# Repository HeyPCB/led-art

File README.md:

# HeyPCB LED Art

Shaped LED boards inspired by films: stars, ghosts, cats, rockets, gears, moons, saucers and shields, each in its own colour. KiCad 10, JLCPCB-ready, CERN-OHL-S-2.0.

<p align="center">                                                 </p>

Every board is its own silhouette and solder-mask colour, with addressable RGB LEDs (XL-2020RGBC-2812B, WS2812B-2020 class) following its outline, a CH32V003 RISC-V controller running at 5 V (so it drives the LEDs directly), a MODE button, a 1-wire SWIO programming header, a 3-pin OUT header that chains the light onto the next board, and USB-C power on a tab at the bottom. 4 layers.

| Board | Idea | Mask | Size | DRC errors / unconnected / parity |
|---|---|---|---|---|
| [Invader](boards/arcade-invader/) | marching down from 1978 | Green | 91.21 x 74.21 mm | 0 / 0 / 0 |
| [Full Moon](boards/big-moon/) | a full moon for a lab window | White | 87.99 x 95 mm | 0 / 0 / 0 |
| [Paw Print](boards/big-paw/) | a paw print from a hero dog film | Purple | 85.1 x 87.71 mm | 0 / 0 / 0 |
| [Clockwork](boards/blast-gear/) | a clockwork gear with a ticking light | Black | 76.01 x 82.08 mm | 0 / 0 / 0 |
| [Heartbeat](boards/broken-heart/) | a heart that beats at your pulse | Red | 82.84 x 81.86 mm | 0 / 0 / 0 |
| [Castle Key](boards/castle-key/) | a black key to the castle | Black | 92.01 x 47.01 mm | 0 / 0 / 0 |
| [Chest Reactor](boards/chest-reactor/) | the glowing chest piece every armoured film hero needs | White | 71.93 x 78.97 mm | 0 / 0 / 0 |
| [Crescent](boards/crescent-moon/) | a crescent moon for a werewolf night | Purple | 80.44 x 91.01 mm | 0 / 0 / 0 |
| [Crystal](boards/crystal/) | a power crystal from a fantasy quest | Purple | 62.01 x 93.01 mm | 0 / 0 / 0 |
| [Deep Sea](boards/deep-fish/) | a deep-sea fish with a glowing lure | Blue | 86.33 x 52.75 mm | 0 / 0 / 0 |
| [Donut](boards/donut/) | a ring with a hole you can see through | Purple | 79.95 x 86.97 mm | 0 / 0 / 0 |
| [Eclipse](boards/eclipse/) | a black ring like a solar eclipse | Black | 79.95 x 86.97 mm | 0 / 0 / 0 |
| [Saucer](boards/flying-saucer/) | a flying saucer from a drive-in movie | Green | 96.01 x 56.67 mm | 0 / 0 / 0 |
| [Forest](boards/forest-leaf/) | a leaf from an enchanted forest | Green | 66.53 x 97.83 mm | 0 / 0 / 0 |
| [Galaxy](boards/galaxy/) | an eight-point star like a galaxy | Purple | 88.01 x 95.01 mm | 0 / 0 / 0 |
| [Ghost Ship](boards/ghost-ship/) | a white saucer that hums at night | White | 100.01 x 58.74 mm | 0 / 0 / 0 |
| [Ghost Trap](boards/ghost-trap/) | a friendly ghost with a pulse | White | 62.01 x 82.76 mm | 0 / 0 / 0 |
| [Haunted](boards/haunted-house/) | a little haunted house with flickering eaves | Black | 76.01 x 86.82 mm | 0 / 0 / 0 |
| [Coin](boards/heptagon-coin/) | a seven-sided coin from a treasure chest | Yellow | 74.11 x 79.25 mm | 0 / 0 / 0 |
| [Hero Shield](boards/hero-shield/) | a hero's shield with a lit rim | Blue | 64.01 x 83.01 mm | 0 / 0 / 0 |
| [Hive Cell](boards/hive-cell/) | a honeycomb cell that tiles | Yellow | 69.3 x 87.01 mm | 0 / 0 / 0 |
| [Hyperdrive](boards/hyperdrive/) | an octagon that counts down to the jump | Black | 77.62 x 84.62 mm | 0 / 0 / 0 |
| [Neon Kitty](boards/kitty-pink/) | a neon cat sign from a rainy street | Red | 58.01 x 83.01 mm | 0 / 0 / 0 |
| [Knight](boards/knight-shield/) | a knight's black shield | Black | 56.01 x 75.01 mm | 0 / 0 / 0 |
| [Koi](boards/koi/) | a red koi from a garden pond | Red | 74.71 x 46.59 mm | 0 / 0 / 0 |
| [Love Letter](boards/lucky-heart/) | a small heart for a long-distance letter | Purple | 67.78 x 68.25 mm | 0 / 0 / 0 |
| [Midnight Cat](boards/midnight-cat/) | a black cat with glowing outline eyes | Black | 66 x 91.01 mm | 0 / 0 / 0 |
| [Monarch](boards/monarch/) | a butterfly whose wings flutter in light | Yellow | 83.16 x 65.2 mm | 0 / 0 / 0 |
| [Moon Rocket](boards/moon-rocket/) | the rocket from a 1950s moon movie | White | 68.01 x 103.01 mm | 0 / 0 / 0 |
| [Nebula](boards/nebula-cloud/) | a purple nebula cloud | Purple | 71.06 x 51.79 mm | 0 / 0 / 0 |
| [Night Wing](boards/night-bat/) | a bat that spreads its wings at dusk | Black | 104.01 x 69.42 mm | 0 / 0 / 0 |
| [Boo](boards/night-ghost/) | a purple ghost that says boo | Purple | 56.01 x 74 mm | 0 / 0 / 0 |
| [Orbit](boards/orbit/) | a black planet with a lit ring | Black | 86.8 x 58.98 mm | 0 / 0 / 0 |
| [Pentagon](boards/pentagon/) | a pentagon for a summoning circle | Green | 79.9 x 82.99 mm | 0 / 0 / 0 |
| [Skull](boards/pirate-skull/) | a pirate flag skull with a lit jaw | Black | 64.01 x 71.89 mm | 0 / 0 / 0 |
| [1Up](boards/power-shroom/) | the power-up from a side-scroller | Red | 86 x 86.12 mm | 0 / 0 / 0 |
| [Red Star](boards/red-star/) | a five-point star that lights up | Red | 87.51 x 90.23 mm | 0 / 0 / 0 |
| [Rock Pick](boards/rock-pick/) | a guitar pick that flashes on the beat | Black | 55.45 x 62.45 mm | 0 / 0 / 0 |
| [Jewel](boards/royal-diamond/) | a ruby from a jewel-heist film | Red | 54.01 x 83.01 mm | 0 / 0 / 0 |
| [Sheriff](boards/sheriff/) | a six-point sheriff's star | Yellow | 76.23 x 95.01 mm | 0 / 0 / 0 |
| [Skeleton Key](boards/skeleton-key/) | the key that opens the secret door | Yellow | 104.01 x 47.01 mm | 0 / 0 / 0 |
| [Snowflake](boards/snow-crystal/) | a snowflake for a winter film | White | 79.69 x 99.01 mm | 0 / 0 / 0 |
| [Halt](boards/stop-sign/) | an octagon that says stop | Red | 73.93 x 80.93 mm | 0 / 0 / 0 |
| [Storm Cloud](boards/storm-cloud/) | a cloud that rains light | White | 80.66 x 56.49 mm | 0 / 0 / 0 |
| [Tin Robot](boards/tin-robot/) | a friendly robot head with an antenna | White | 84.01 x 83.61 mm | 0 / 0 / 0 |
| [Little Green](boards/ufo-green/) | a black saucer with green running lights | Black | 84 x 50.47 mm | 0 / 0 / 0 |
| [Vampire](boards/vampire/) | a red bat for a vampire film | Red | 92.01 x 62.21 mm | 0 / 0 / 0 |
| [Engine Room](boards/war-gear/) | a gear from the engine room of a steam airship | Blue | 80.01 x 86.51 mm | 0 / 0 / 0 |
| [Wizard](boards/wizard-star/) | a seven-point star from a wizard's robe | Blue | 85.81 x 90.66 mm | 0 / 0 / 0 |
| [Winter Tree](boards/xmas-tree/) | a pine tree for a winter holiday film | Green | 80.01 x 81.01 mm | 0 / 0 / 0 |

**Not fabricated, assembled or powered.** Every number in a board's README is measured by KiCad 10 on the files in its folder (`report.json`); parts carry LCSC numbers and were in JLCPCB's stock on the date each README gives. Order each board in its stated mask colour. Firmware is not included: these are the boards.

Designed with the HeyPCB method on KiCad 10 by heypcb-kicad's headless pipeline with Freerouting 2.4.1.

## Licence

CERN-OHL-S-2.0, © 2026 heypcb.ai. See [LICENSE](LICENSE).

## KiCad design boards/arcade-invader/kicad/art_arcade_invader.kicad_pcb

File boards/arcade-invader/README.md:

# INVADER

marching down from 1978

| Layers | Size | Parts | Nets | Connections routed | Vias | ERC errors | DRC errors / unconnected / parity |
|---|---|---|---|---|---|---|---|
| 4 | 91.21 x 74.21 mm | 54 | 32 | 138 -> 0 open | 144 | 0 | 0 / 0 / 0 |

**Not fabricated, assembled or powered.** Every number on this page is measured by KiCad 10 on the files in this folder; the full measurements are in [`report.json`](report.json).

| | |
|---|---|
| KiCad project | [`kicad/`](kicad/) |
| Gerbers, BOM, CPL, STEP, schematic PDF | [`fab/`](fab/) |
| Renders | [top](media/top.png), [bottom](media/bottom.png) |

A pixel alien from the arcade era, marching down the screen in blocky steps. The people who wrote those games lost a lot of coins to them first. Designed with the HeyPCB method on KiCad 10, by heypcb-kicad's headless pipeline with Freerouting 2.4.1, from the brief in `board.json`.

## Specs

- **Shape:** invader, 91.21 x 74.21 mm, green solder mask, 4 layers, 1.6 mm. A 16 mm tab at the bottom carries the USB-C receptacle.
- **Light:** 21 XL-2020RGBC-2812B addressable RGB LEDs (WS2812B-2020 class, 2 x 2 mm) chained around the outline, each with its own 100 nF.
- **Controller:** CH32V003F4P6 RISC-V MCU at 5 V (so its data output meets the LEDs' 5 V logic with no translator), programmed over the 1-wire SWIO header with a WCH-LinkE; MODE button on PC0.
- **Power:** USB-C 5 V (5.1k on CC1 and CC2). 21 LEDs at full white would draw about 0.8 A, so firmware caps brightness to stay inside a 0.5 A USB port (about 14 % average).

## Parts

Every line carries an LCSC part number. Stock is JLCPCB's assembly stock on 2026-10-19.

| Designators | Value | LCSC | MPN | JLCPCB tier | Stock |
|---|---|---|---|---|---|
| C1,C2 | 10uF | C15850 | CL21A106KAYNNNE | Basic | 6,481,857 |
| C3,C4,C5,C6,C7,C8,C9,C10,C11,C12,C13,C14,C15,C16,C17,C18,C19,C20,C21,C22,C23,C24 | 100nF | C1525 | CL05B104KO5NNNC | Basic | 29,476,420 |
| D1,D2,D3,D4,D5,D6,D7,D8,D9,D10,D11,D12,D13,D14,D15,D16,D17,D18,D19,D20,D21 | XL-2020RGBC-2812B | C5349955 | XL-2020RGBC-2812B | Extended | 100,374 |
| J1 | USB-C | C165948 | TYPE-C-31-M-12 | Extended | 357,307 |
| J2 | SWIO | C2937625 | PZ254V-11-03P | Extended | 924,821 |
| J3 | OUT | C2937625 | PZ254V-11-03P | Extended | 924,821 |
| R1,R2 | 5.1k | C25905 | 0402WGF5101TCE | Basic | 5,086,543 |
| R3 | 33 | C23140 | 0603WAF330JT5E | Basic | 4,946,796 |
| R4 | 10k | C25804 | 0603WAF1002T5E | Basic | 39,931,112 |
| SW1 | MODE | C318884 | TS-1187A-B-A-B | Basic | 290,976 |
| U1 | CH32V003F4P6 | C5187096 | CH32V003F4P6 | Extended | 26,142 |

## Ordering

- PCB: upload `fab/art_arcade_invader_gerbers.zip`, 4 layers, 91.21 x 74.21 mm, 1.6 mm, green solder mask with white silkscreen.
- Assembly: `fab/art_arcade_invader_bom.csv` and `fab/art_arcade_invader_cpl_jlc.csv`, top side.
- The CPL is fitted to each part's own JLCPCB footprint, pad by pad, and re-checked by laying each footprint where its row says: 53 of 54 rows fitted, worst pin-to-pad offset 0.26 mm.
- Not fitted (no JLCPCB footprint to fit to), rotation from KiCad's: SW1. Check these in JLCPCB's placement preview.

## Notes

- The USB-C receptacle renders as a plain box: KiCad's footprint names a 3D model KiCad does not ship.
- Firmware is not part of this repository: the board is the hardware. Not built or measured.

## How it was made

Designed with the HeyPCB method on KiCad 10, by heypcb-kicad's headless pipeline with Freerouting 2.4.1, from the brief in [`board.json`](board.json).

## Licence

CERN-OHL-S-2.0, © 2026 heypcb.ai. See the collection's LICENSE.

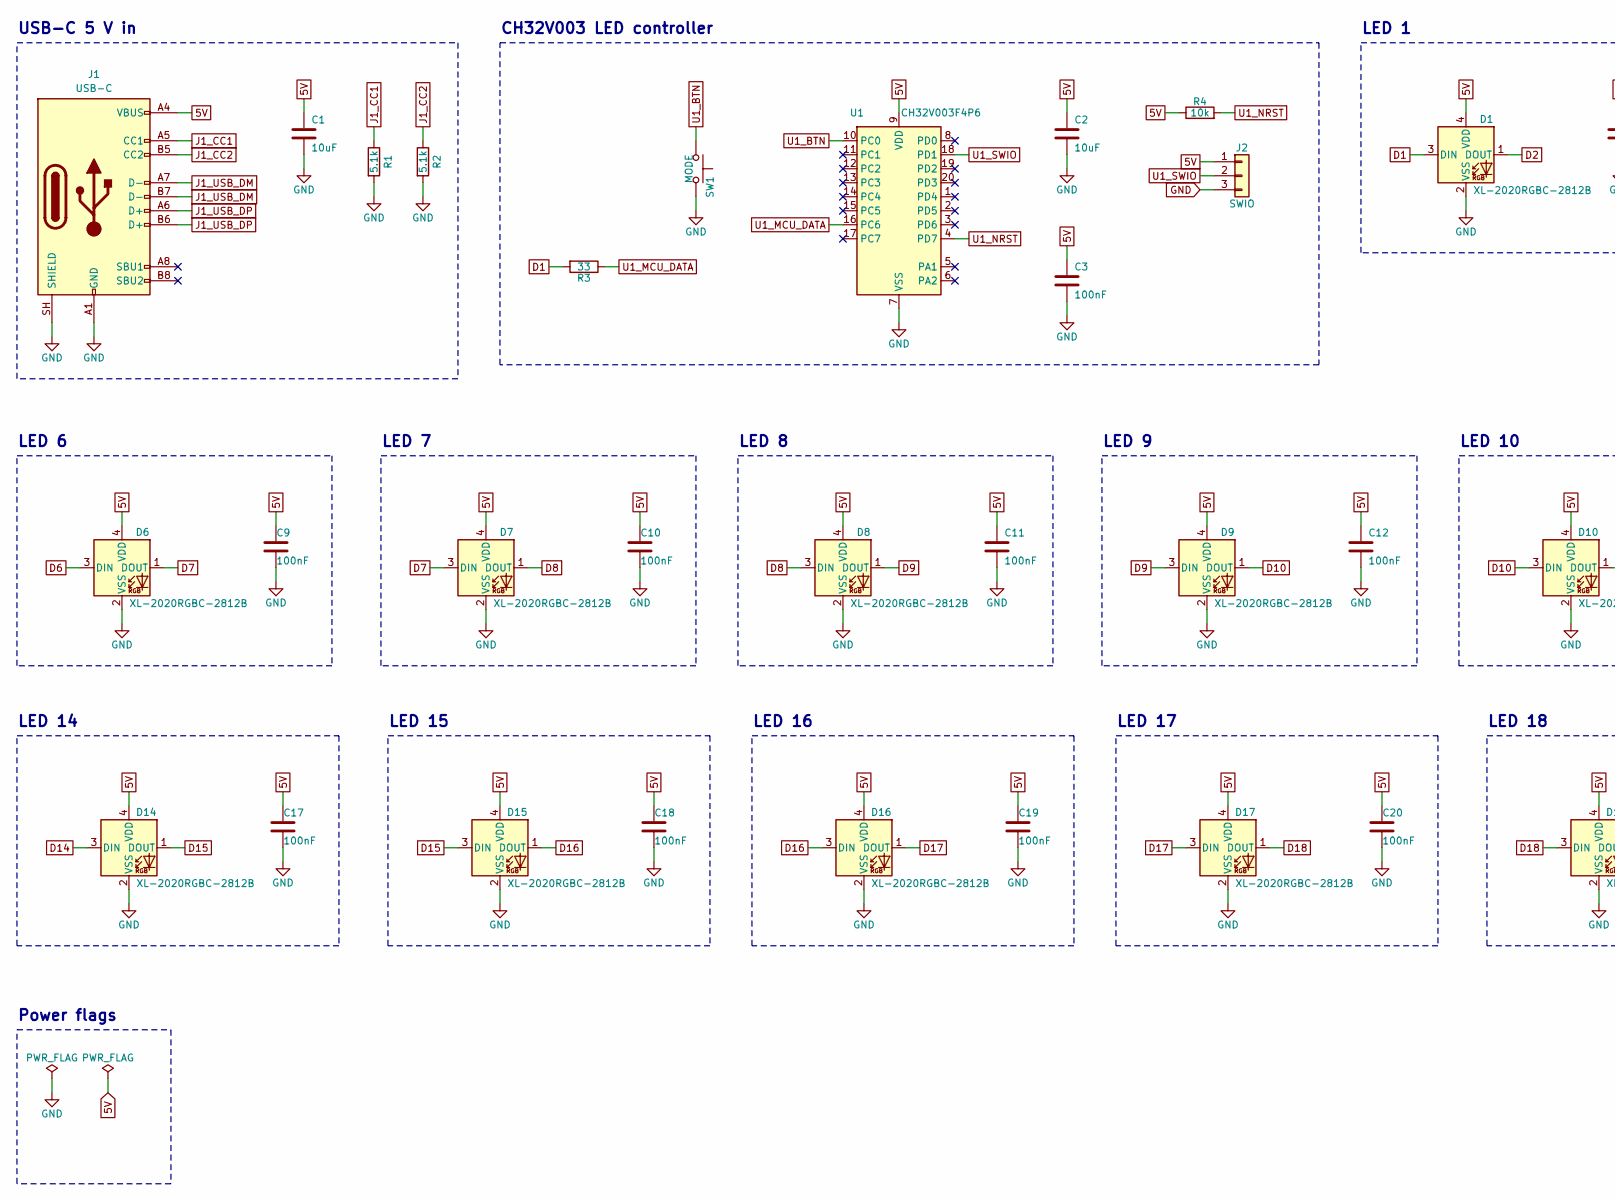
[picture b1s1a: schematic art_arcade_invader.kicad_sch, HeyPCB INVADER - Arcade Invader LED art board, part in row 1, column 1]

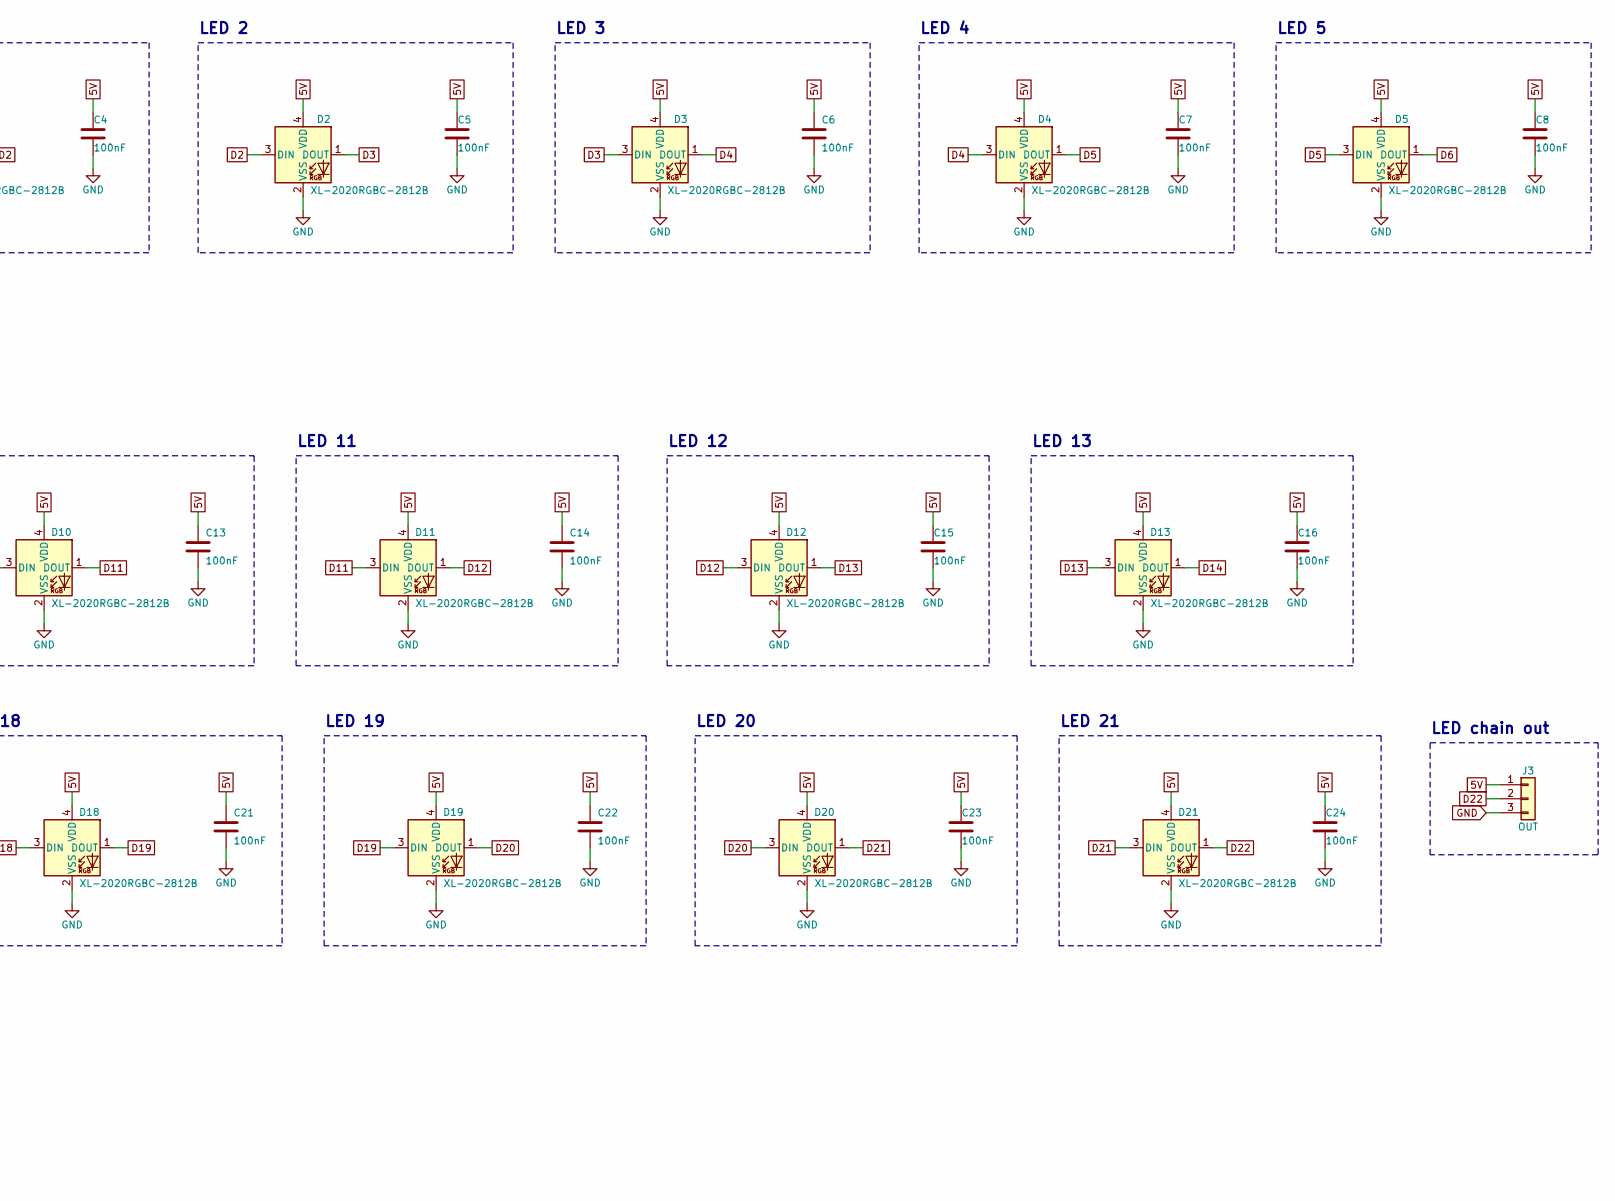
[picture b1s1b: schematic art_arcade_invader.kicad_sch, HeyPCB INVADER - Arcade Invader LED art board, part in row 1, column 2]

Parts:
C1, C2: 10uF; C_0805_2012Metric; MPN CL21A106KAYNNNE; LCSC C15850
C3, C4, C5, C6, C7, C8, C9, C10, C11, C12, C13, C14, C15, C16, C17, C18, C19, C20, C21, C22, C23, C24: 100nF; C_0402_1005Metric; MPN CL05B104KO5NNNC; LCSC C1525
D1, D2, D3, D4, D5, D6, D7, D8, D9, D10, D11, D12, D13, D14, D15, D16, D17, D18, D19, D20, D21: XL-2020RGBC-2812B; LED_WS2812B-2020_PLCC4_2.0x2.0mm; MPN XL-2020RGBC-2812B; LCSC C5349955
J1: USB-C; USB_C_Receptacle_HRO_TYPE-C-31-M-12; MPN TYPE-C-31-M-12; LCSC C165948
J2: SWIO; PinHeader_1x03_P2.54mm_Vertical; MPN PZ254V-11-03P; LCSC C2937625
J3: OUT; PinHeader_1x03_P2.54mm_Vertical; MPN PZ254V-11-03P; LCSC C2937625
R1, R2: 5.1k; R_0402_1005Metric; MPN 0402WGF5101TCE; LCSC C25905
R3: 33; R_0603_1608Metric; MPN 0603WAF330JT5E; LCSC C23140
R4: 10k; R_0603_1608Metric; MPN 0603WAF1002T5E; LCSC C25804
SW1: MODE; SW_Push_1P1T_XKB_TS-1187A; MPN TS-1187A-B-A-B; LCSC C318884
U1: CH32V003F4P6; TSSOP-20_4.4x6.5mm_P0.65mm; MPN CH32V003F4P6; LCSC C5187096

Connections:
5V: C1.1, C2.1, C3.1, C4.1, C5.1, C6.1, C7.1, C8.1, C9.1, C10.1, C11.1, C12.1, C13.1, C14.1, C15.1, C16.1, C17.1, C18.1, C19.1, C20.1, C21.1, C22.1, C23.1, C24.1, D1.4 (VDD), D2.4 (VDD), D3.4 (VDD), D4.4 (VDD), D5.4 (VDD), D6.4 (VDD), D7.4 (VDD), D8.4 (VDD), D9.4 (VDD), D10.4 (VDD), D11.4 (VDD), D12.4 (VDD), D13.4 (VDD), D14.4 (VDD), D15.4 (VDD), D16.4 (VDD), D17.4 (VDD), D18.4 (VDD), D19.4 (VDD), D20.4 (VDD), D21.4 (VDD), J1.A4 (VBUS), J1.A9 (VBUS), J1.B4 (VBUS), J1.B9 (VBUS), J2.1, J3.1, R4.1, U1.9 (VDD)
D1: D1.3 (DIN), R3.2
D2: D1.1 (DOUT), D2.3 (DIN)
D3: D2.1 (DOUT), D3.3 (DIN)
D4: D3.1 (DOUT), D4.3 (DIN)
D5: D4.1 (DOUT), D5.3 (DIN)
D6: D5.1 (DOUT), D6.3 (DIN)
D7: D6.1 (DOUT), D7.3 (DIN)
D8: D7.1 (DOUT), D8.3 (DIN)
D9: D8.1 (DOUT), D9.3 (DIN)
D10: D9.1 (DOUT), D10.3 (DIN)
D11: D10.1 (DOUT), D11.3 (DIN)
D12: D11.1 (DOUT), D12.3 (DIN)
D13: D12.1 (DOUT), D13.3 (DIN)
D14: D13.1 (DOUT), D14.3 (DIN)
D15: D14.1 (DOUT), D15.3 (DIN)
D16: D15.1 (DOUT), D16.3 (DIN)
D17: D16.1 (DOUT), D17.3 (DIN)
D18: D17.1 (DOUT), D18.3 (DIN)
D19: D18.1 (DOUT), D19.3 (DIN)
D20: D19.1 (DOUT), D20.3 (DIN)
D21: D20.1 (DOUT), D21.3 (DIN)
D22: D21.1 (DOUT), J3.2
GND: C1.2, C2.2, C3.2, C4.2, C5.2, C6.2, C7.2, C8.2, C9.2, C10.2, C11.2, C12.2, C13.2, C14.2, C15.2, C16.2, C17.2, C18.2, C19.2, C20.2, C21.2, C22.2, C23.2, C24.2, D1.2 (VSS), D2.2 (VSS), D3.2 (VSS), D4.2 (VSS), D5.2 (VSS), D6.2 (VSS), D7.2 (VSS), D8.2 (VSS), D9.2 (VSS), D10.2 (VSS), D11.2 (VSS), D12.2 (VSS), D13.2 (VSS), D14.2 (VSS), D15.2 (VSS), D16.2 (VSS), D17.2 (VSS), D18.2 (VSS), D19.2 (VSS), D20.2 (VSS), D21.2 (VSS), J1.A1 (GND), J1.A12 (GND), J1.B1 (GND), J1.B12 (GND), J1.SH (SHIELD), J2.3, J3.3, R1.2, R2.2, SW1.2, U1.7 (VSS)
J1_CC1: J1.A5 (CC1), R1.1
J1_CC2: J1.B5 (CC2), R2.1
J1_USB_DM: J1.A7 (D-), J1.B7 (D-)
J1_USB_DP: J1.A6 (D+), J1.B6 (D+)
U1_BTN: SW1.1, U1.10 (PC0)
U1_MCU_DATA: R3.1, U1.16 (PC6)
U1_NRST: R4.2, U1.4 (PD7)
U1_SWIO: J2.2, U1.18 (PD1)

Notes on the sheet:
USB-C 5 V in
CH32V003 LED controller
LED 1
LED 2
LED 3
LED 4
LED 5
LED 6
LED 7
LED 8
LED 9
LED 10
LED 11
LED 12
LED 13
LED 14
LED 15
LED 16
LED 17
LED 18
LED 19
LED 20
LED 21
LED chain out
Power flags

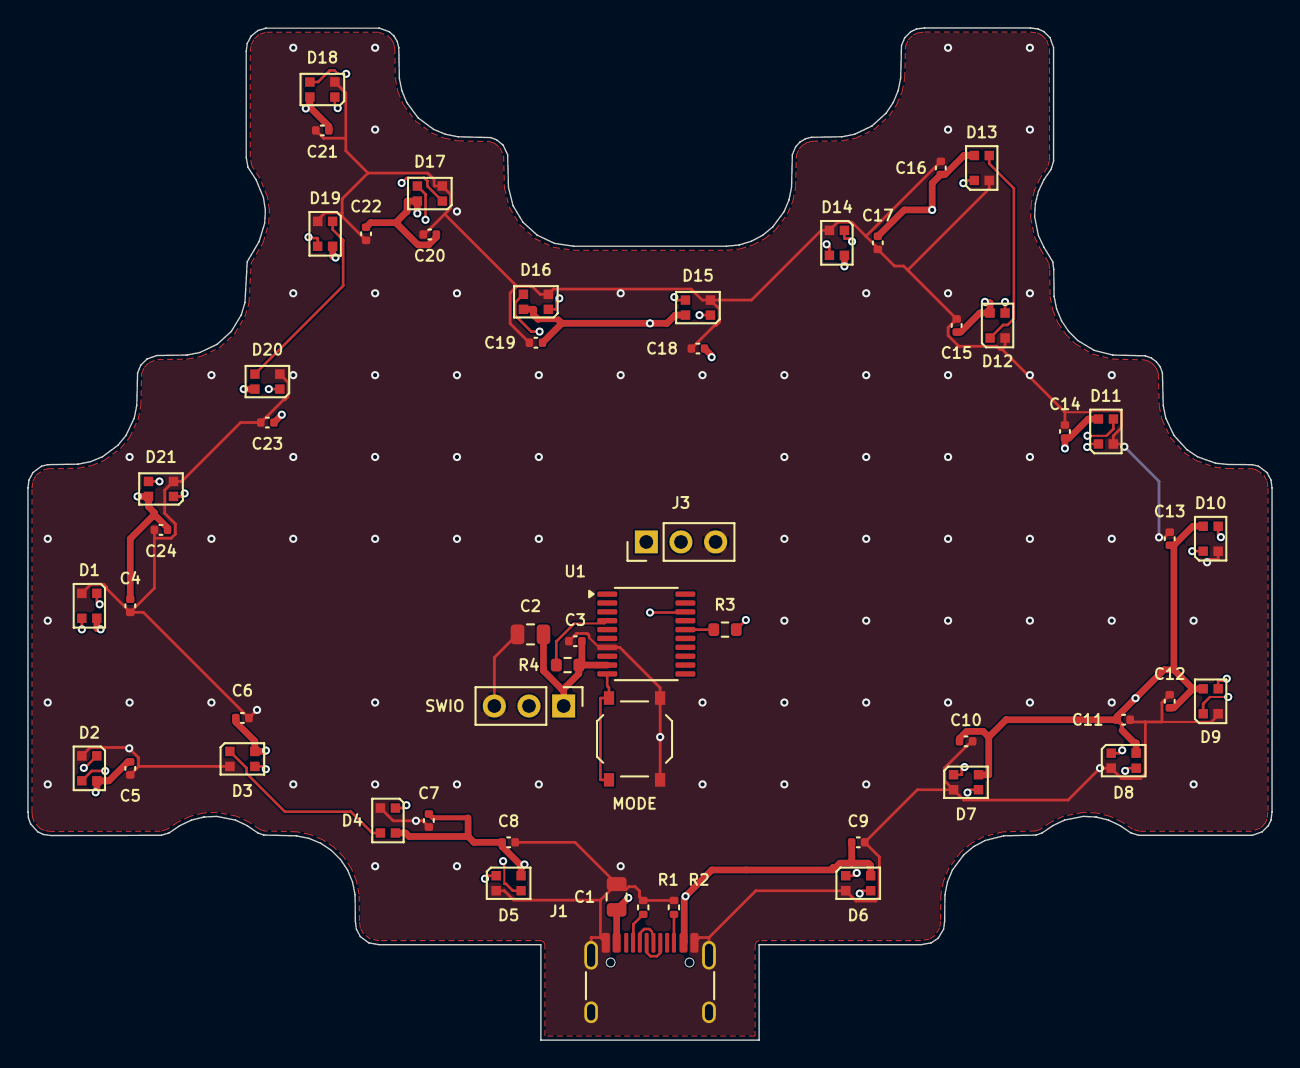
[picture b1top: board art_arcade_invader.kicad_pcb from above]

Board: 4 copper layers, 91.2 x 74.2 mm, 54 parts (0 on the bottom side), 32 nets.
